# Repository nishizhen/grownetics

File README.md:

# Grownetics

Welcome to Grownetics Open Source repository.

Grownetics is a platform to help the world learn how to grow every plant better.

This repository will contain as much as we can possibly open source.

## Repository Status

Until recently all of our source was closed. We are moving to open as much of it as we can. As we do that, there will be problems, bugs, etc. This repository can be considered unstable.

# Handbook

[Grownetics Company Handbook](http://docs.grownetics.co/)

[Using our Documentation](http://docs.grownetics.co/documentation/)

# Technical Documentation

* [GrowServer](http://docs.grownetics.co/Development/growserver/)
* [Firmware](http://docs.grownetics.co/Development/firmware/)
* [GrowCtl](http://docs.grownetics.co/Development/growctl/)

# Reporting bugs

If you find a bug with the documentation, or something that could be improved, please open an [issue](https://code.cropcircle.io/Grownetics/Grownetics/issues).

# Community

Please join us and let us know what you think!

## [Chat](https://grownetics.zulipchat.com/)
## [Reddit](https://reddit.com/r/Grownetics/)
## [Twitch](https://www.twitch.tv/nickbusey/)

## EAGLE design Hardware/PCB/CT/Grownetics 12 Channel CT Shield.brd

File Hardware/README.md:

[< Documentation](../README.md)
# Hardware
### [Production](hardware-production.md)

### Arduino Software Setup
1. Download [VSCode](https://code.visualstudio.com/Download)  
2. Open the Extensions menu and install PlatformIO IDE (http://docs.platformio.org/en/latest/ide/vscode.html#installation)  
3. After platform.io is downloaded in vscode restart vscode, it will initiate the install, upon completion a bar comes on up top to restart vscode. You're in!  

### Git the Grownetics Repo   
1. Download and Install [git](http://git-scm.com/download/mac) (already installed on linux)  
2. 'cd' to the folder you want the Grownetics Repo to be in  
3. Check out the code (open Terminal and copy-paste)
`git clone git@code.cropcircle.io:Grownetics/Grownetics.git`
if you are unable to authenticate login to gitlab via code.cropcircle.io and add your .ssh public key to your profile settings. Then try again.  
4. Back in platform.io open the firmware folder you want to work with.  (i.e. the Middleware folder)
5. Navigate to the src folder once the project folder is open, click the Middleware.ino file
6. Build the file by clicking the tiny check mark at the bottom of the vscode window. 
7. You may have a missing library, this is where platform.io is awesome! Click the PIO Home tab
8. Click Libraries in the PIO left menu, search for the missing library (case and spaces matter!)
9. Click install, and try your build again, should be gtg!
5. Click the little right hand arrow at bottom of vscode to Upload it to the board.

### Arduino/Wifi-Reset Software Testing
1. Make sure you have the latest code by running `git pull` within the project folder.
2. Turn on Server/Pepwave, make sure TP-Links are synced, and make sure the Arduino Ethernet Shield has an ethernet cord out to the POE device connected to one of the TP-Links.
3. Verify/Upload the 'Middleware.x.x.x.ino' code to the Arduino.
4. Open the serial monitor (Cmd/Ctrl+Shift+M) and make sure data is accurately coming out AND that the server is sending a response back to the Arduino. 
  * ***Uploading code to the Arduino while the WiFi-Reset is ON can sometimes cause problems. Try uploading with the WiFi-Reset OFF.***  
  * ***The serial monitor has specific baud (data rate in bits per second) values that it receives output from. Make sure your serial monitor is set to the same baud value as in the code to see the correct output.***  

5. Verify/Upload the 'ESP8266_WiFi_Reset.x.x.x.ino' code directly to the WiFi-Reset module. 
6. Open the serial monitor and make sure it's getting a status code of 200 from the Server. If not, make sure the Access Point (Pepwave) login credentials match with the credentials in the wifi reset code.

7. The Arduino and WiFi Reset devices have been successfully tested, to be ready for production: Set debug = false, and assign an ID to the device (starting at 1).

## 3D Crop Sensor

3D Crop Device: onsite.grownetics.co port 81
Reset Device: onsite.grownetics.co port 82

Assembly: Devices should have already passed their individual QC test

Components required (Multiplexer shield, Ethernet shield, Arduino Mega)

*  Before assembly check that all pins are straight and undamaged
*  Match Pins on Arduino Mega with pins on Ethernet shield and connect devices
*  Attach multiplexer shield to the Ethernet shield 

QC Assesment (Device in NEMA box)

*  Make sure device has rubber studs or Velcro to secure it to the base of the NEMA box
*  Insert POE power cable into Arduino mega 
*  Insert other POE cable into Ethernet shield

## Suppliers

### Rapid PCB Suppliers
1. http://www.pcbway.com/f
2. http://www.pentalogix.com/pcb-manufacturing.php?gclid=CLmT5YOP_csCFQmSaQodgkoIUw
3. https://www.itead.cc/
4. http://www.customcircuitboards.com/
5. http://www.pcb-solutions.com/
6. http://www.pcbunlimited.com/
7. http://www.4pcb.com/
8. http://www.goldphoenixpcb.com/
9. http://www.seeedstudio.com/service/index.php?r=pcb

#### Pepwave Max BR-1
 * Support Contact:  taylor@frontierus.com, jgrote@frontierus.com, tel:866-226-6344
 * Default Wifi Password: Last 8 digits of LAN MAC.
 * Default admin login: admin/admin

* SIM Cards
 * Verizon Business Support:

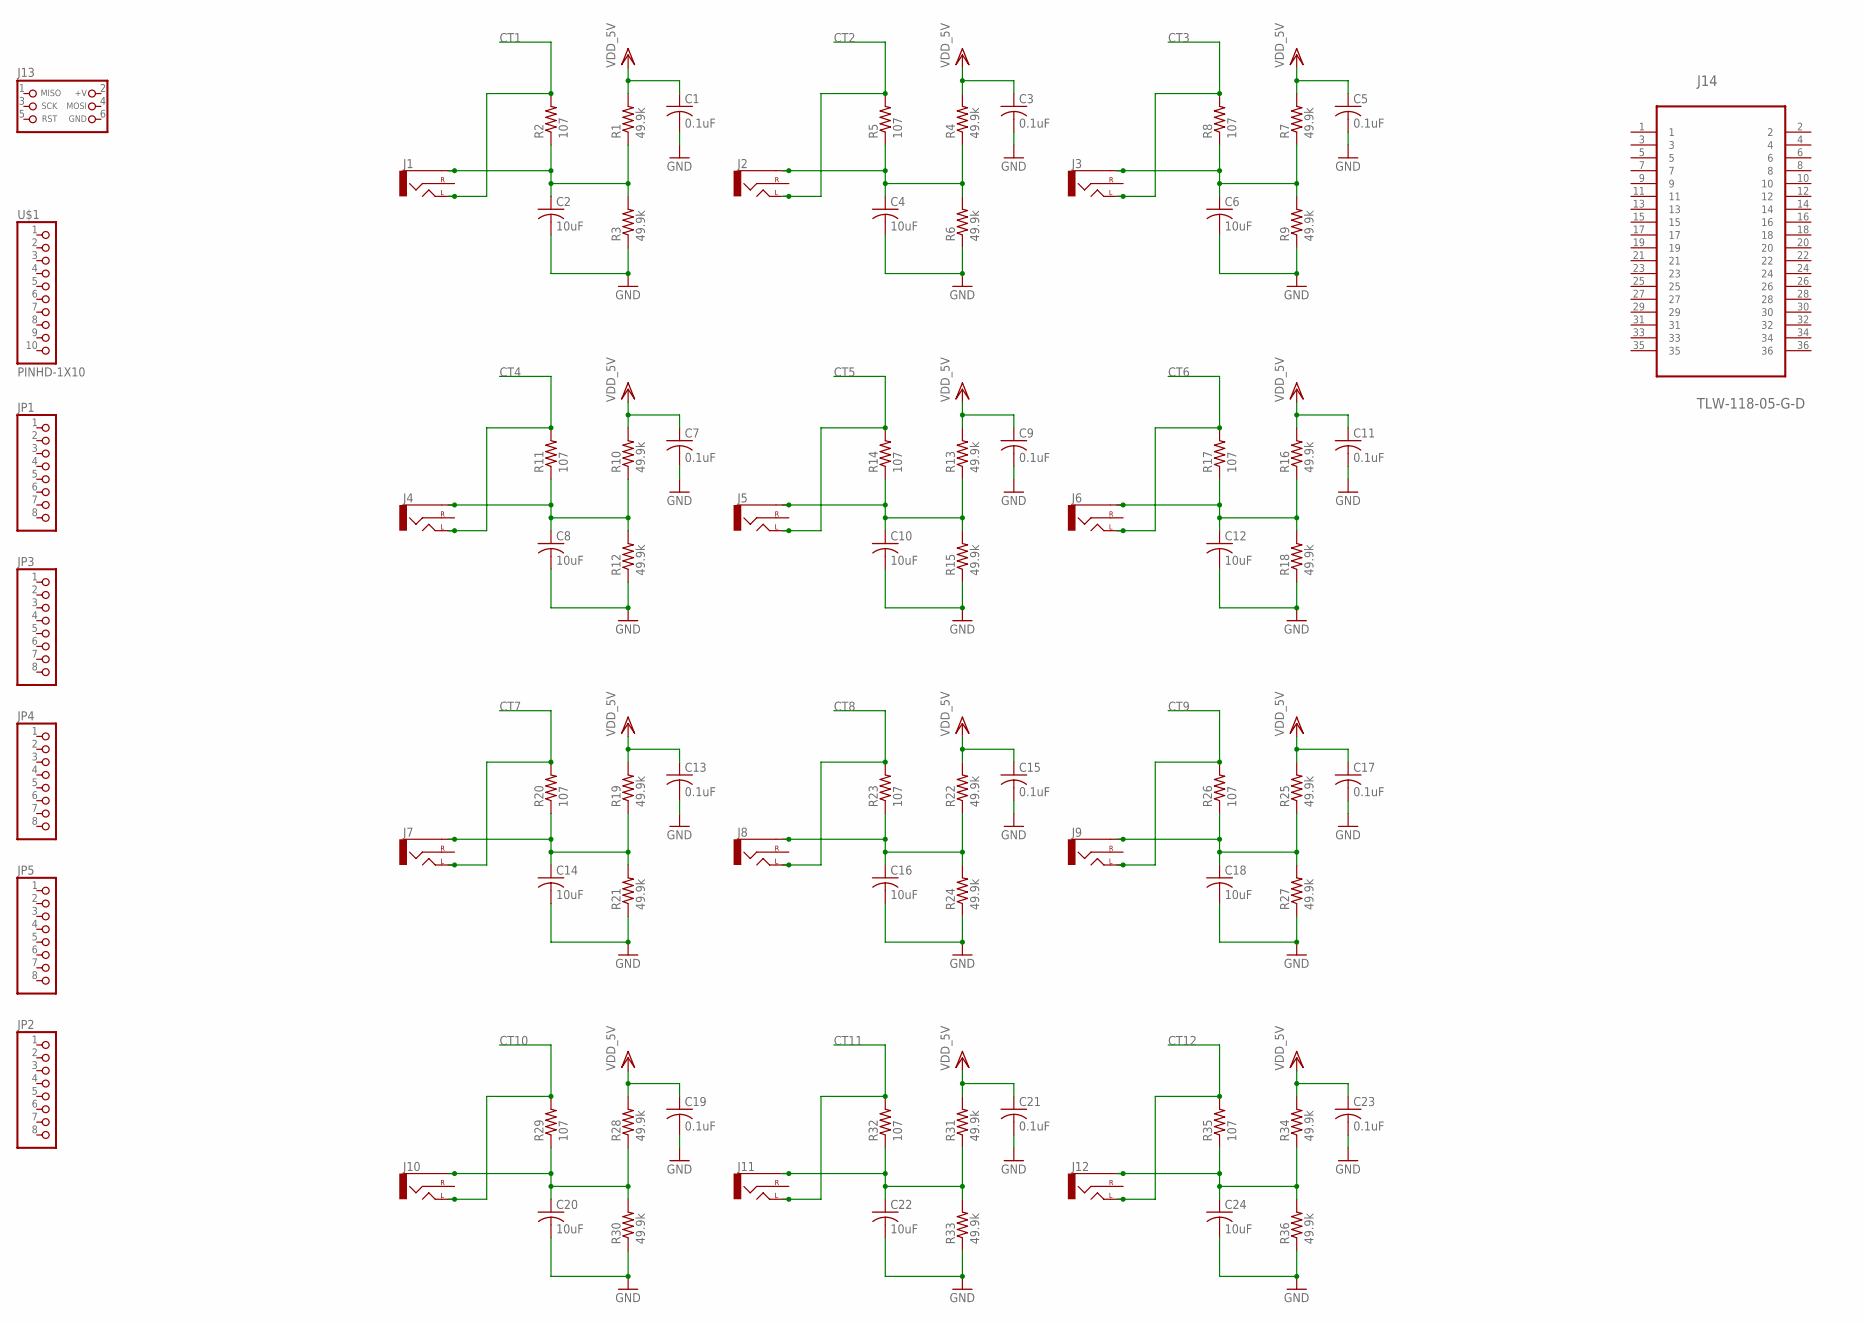
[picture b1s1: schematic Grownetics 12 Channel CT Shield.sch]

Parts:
C1, C3, C5, C7, C9, C11, C13, C15, C17, C19, C21, C23: 0.1uF; C0805
C2, C4, C6, C8, C10, C12, C14, C16, C18, C20, C22, C24: 10uF; C0805
J1, J2, J3, J4, J5, J6, J7, J8, J9, J10, J11, J12: AUDIO-JACKSMD2; AUDIO-JACK-3.5MM-SMD
J13: CON_HEADER_PRG_AVR_ICSP-PTH; HEADER_PRG_2X03
J14: TLW-118-05-G-D; SAMTEC_TLW-118-05-G-D
JP1, JP2, JP3, JP4, JP5: PINHD-1X8-3.5MM; 1X08-3.5MM
R1, R3, R4, R6, R7, R9, R10, R12, R13, R15, R16, R18, R19, R21, R22, R24, R25, R27, R28, R30, R31, R33, R34, R36: 49.9k; M0805
R2, R5, R8, R11, R14, R17, R20, R23, R26, R29, R32, R35: 107; M0805
U$1: PINHD-1X10; 1X10-BIG

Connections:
CT1: J1.TIP (LEFT), R2.2
CT2: J2.TIP (LEFT), R5.2
CT3: J3.TIP (LEFT), R8.2
CT4: J4.TIP (LEFT), R11.2
CT5: J5.TIP (LEFT), R14.2
CT6: J6.TIP (LEFT), R17.2
CT7: J7.TIP (LEFT), R20.2
CT8: J8.TIP (LEFT), R23.2
CT9: J9.TIP (LEFT), R26.2
CT10: J10.TIP (LEFT), R29.2
CT11: J11.TIP (LEFT), R32.2
CT12: J12.TIP (LEFT), R35.2
GND: C1.2, C2.2, C3.2, C4.2, C5.2, C6.2, C7.2, C8.2, C9.2, C10.2, C11.2, C12.2, C13.2, C14.2, C15.2, C16.2, C17.2, C18.2, C19.2, C20.2, C21.2, C22.2, C23.2, C24.2, R3.1, R6.1, R9.1, R12.1, R15.1, R18.1, R21.1, R24.1, R27.1, R30.1, R33.1, R36.1
unnamed: C4.1, J2.SLEEVE, R4.1, R5.1, R6.2
unnamed: C2.1, J1.SLEEVE, R1.1, R2.1, R3.2
unnamed: C6.1, J3.SLEEVE, R7.1, R8.1, R9.2
unnamed: C8.1, J4.SLEEVE, R10.1, R11.1, R12.2
unnamed: C10.1, J5.SLEEVE, R13.1, R14.1, R15.2
unnamed: C12.1, J6.SLEEVE, R16.1, R17.1, R18.2
unnamed: C14.1, J7.SLEEVE, R19.1, R20.1, R21.2
unnamed: C16.1, J8.SLEEVE, R22.1, R23.1, R24.2
unnamed: C18.1, J9.SLEEVE, R25.1, R26.1, R27.2
unnamed: C20.1, J10.SLEEVE, R28.1, R29.1, R30.2
unnamed: C22.1, J11.SLEEVE, R31.1, R32.1, R33.2
unnamed: C24.1, J12.SLEEVE, R34.1, R35.1, R36.2
VDD: C1.1, C3.1, C5.1, C7.1, C9.1, C11.1, C13.1, C15.1, C17.1, C19.1, C21.1, C23.1, R1.2, R4.2, R7.2, R10.2, R13.2, R16.2, R19.2, R22.2, R25.2, R28.2, R31.2, R34.2

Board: 2 copper layers, 80 parts (0 on the bottom side), 26 nets, no tracks yet.

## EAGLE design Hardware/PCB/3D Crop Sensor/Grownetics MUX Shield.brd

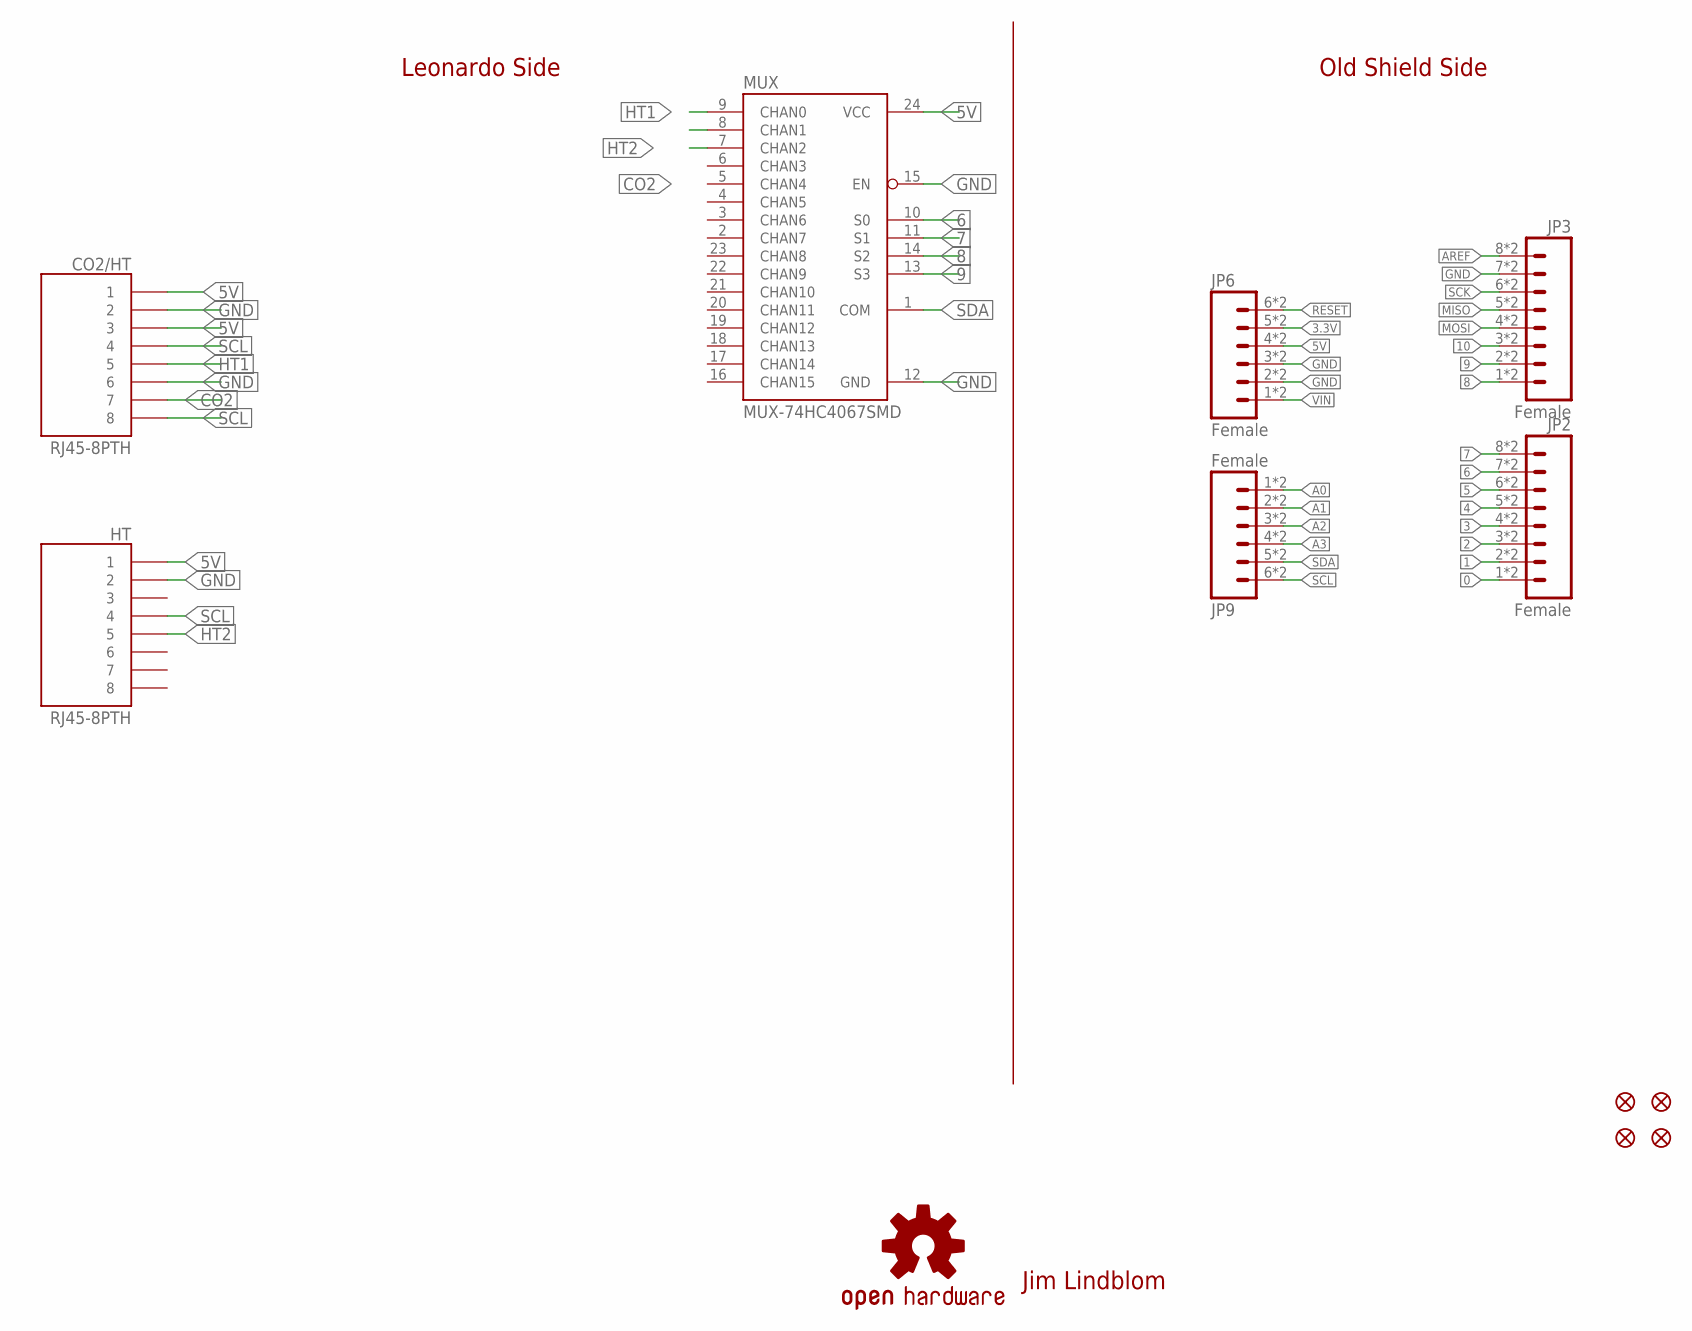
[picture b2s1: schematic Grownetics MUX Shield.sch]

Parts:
CO2/HT: RJ45-8PTH; RJ45-8
HT: RJ45-8PTH; RJ45-8
JP2, JP3: Female; 1X08_SMD_COMBINED
JP6, JP9: Female; 1X06_SMD_STRAIGHT_COMBO
JP11, JP12, JP13, JP14: FIDUCIALUFIDUCIAL; MICRO-FIDUCIAL
MUX: MUX-74HC4067SMD; SSOP24
U$1: OSHW-LOGOS; OSHW-LOGO-S

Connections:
0: JP2.1, JP2.1@2 (1)
1: JP2.2, JP2.2@2 (2)
2: JP2.3, JP2.3@2 (3)
3: JP2.4, JP2.4@2 (4)
3.3V: JP6.5, JP6.5-2 (5)
4: JP2.5, JP2.5@2 (5)
5: JP2.6, JP2.6@2 (6)
5V: CO2/HT.1, CO2/HT.3, HT.1, JP6.4, JP6.4-2 (4), MUX.24 (VCC)
6: JP2.7, JP2.7@2 (7), MUX.10 (S0)
7: JP2.8, JP2.8@2 (8), MUX.11 (S1)
8: JP3.1, JP3.1@2 (1), MUX.14 (S2)
9: JP3.2, JP3.2@2 (2), MUX.13 (S3)
10: JP3.3, JP3.3@2 (3)
A0: JP9.1, JP9.1-2 (1)
A1: JP9.2, JP9.2-2 (2)
A2: JP9.3, JP9.3-2 (3)
A3: JP9.4, JP9.4-2 (4)
AREF: JP3.8, JP3.8@2 (8)
CO2: CO2/HT.7, MUX.7 (CHAN2)
GND: CO2/HT.2, CO2/HT.6, HT.2, JP3.7, JP3.7@2 (7), JP6.2, JP6.2-2 (2), JP6.3, JP6.3-2 (3), MUX.12 (GND), MUX.15 (EN)
HT1: CO2/HT.5, MUX.9 (CHAN0)
HT2: HT.5, MUX.8 (CHAN1)
MISO: JP3.5, JP3.5@2 (5)
MOSI: JP3.4, JP3.4@2 (4)
RESET: JP6.6, JP6.6-2 (6)
SCK: JP3.6, JP3.6@2 (6)
SCL: CO2/HT.4, CO2/HT.8, HT.4, JP9.6, JP9.6-2 (6)
SDA: JP9.5, JP9.5-2 (5), MUX.1 (COM)
VIN: JP6.1, JP6.1-2 (1)

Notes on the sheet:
Jim Lindblom
Leonardo Side
Old Shield Side

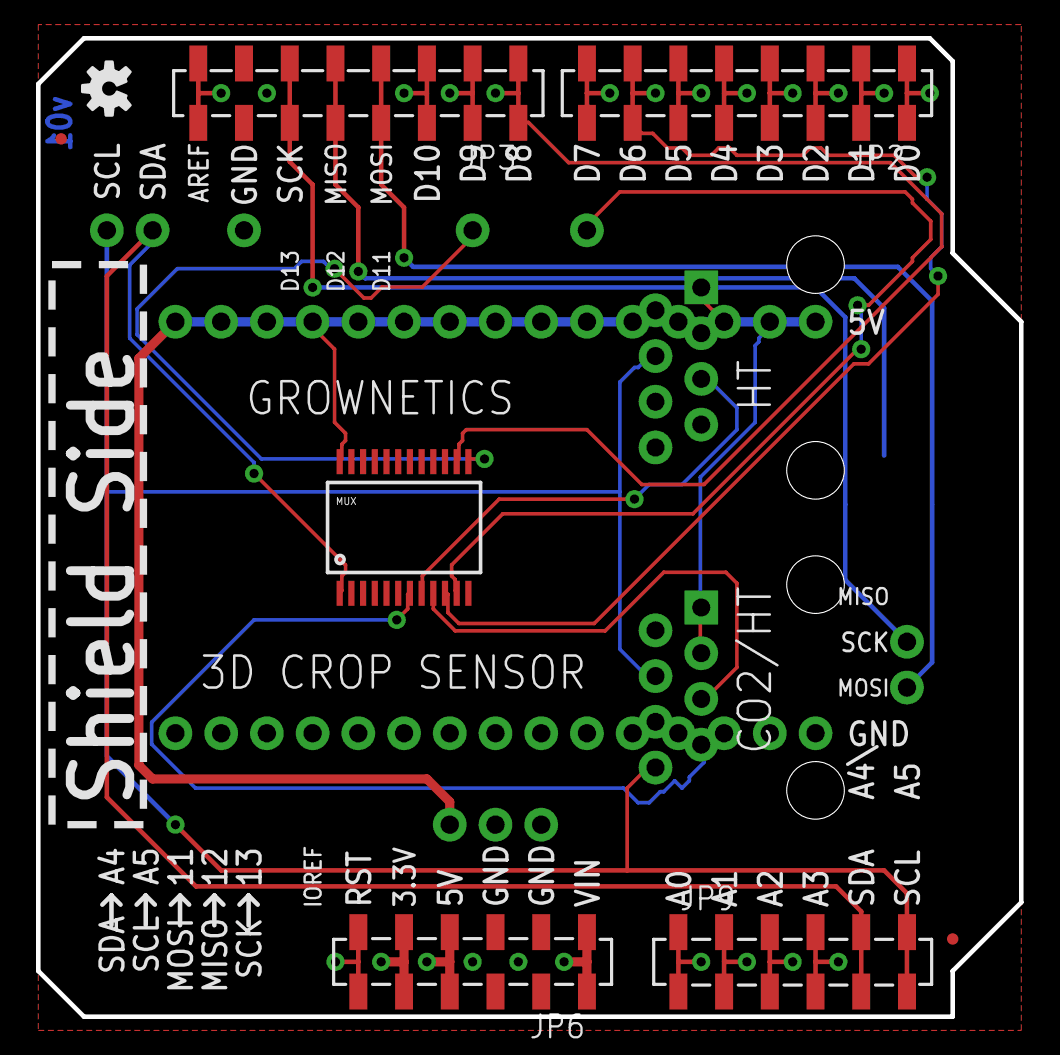
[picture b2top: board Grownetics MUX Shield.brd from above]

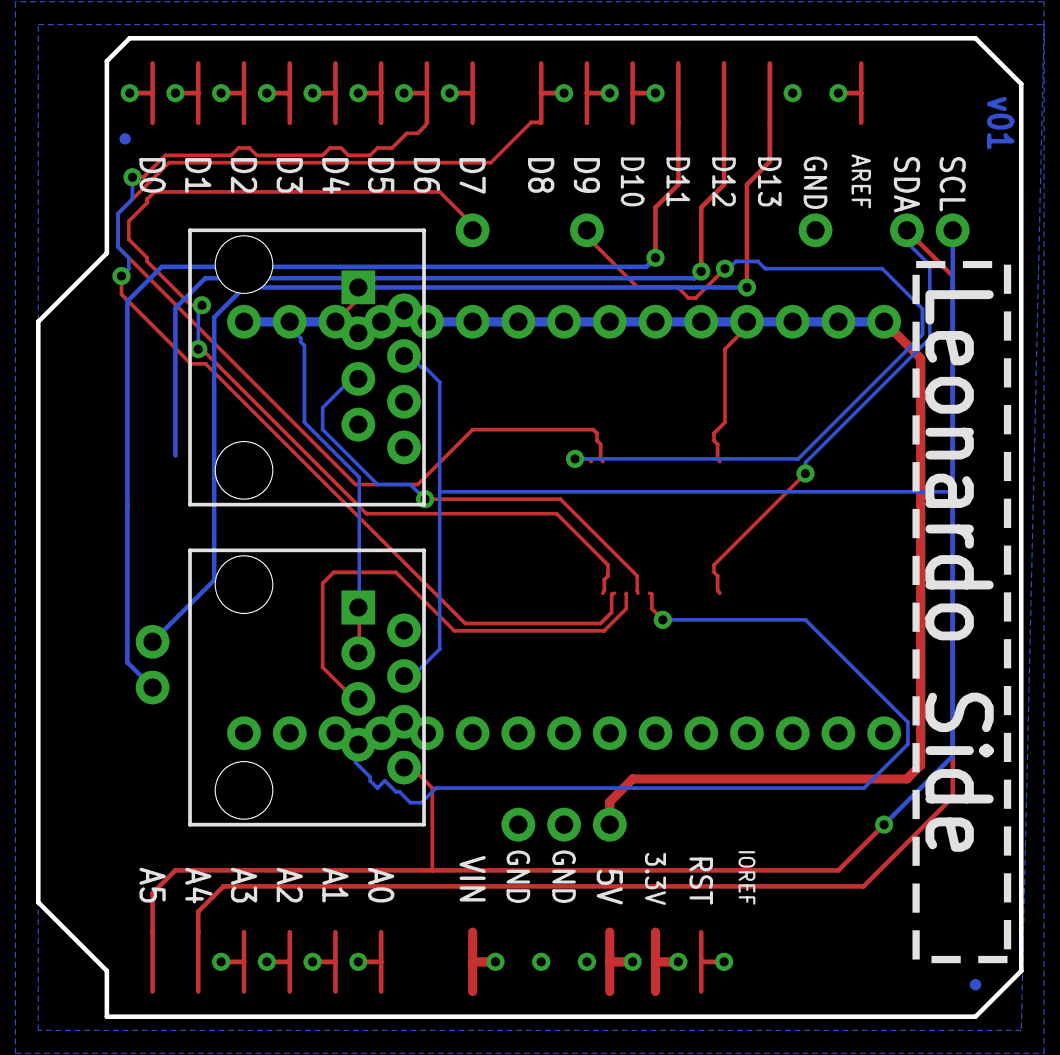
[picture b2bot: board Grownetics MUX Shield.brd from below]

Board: 2 copper layers, 54.6 x 54.4 mm, 12 parts (4 on the bottom side), 29 nets.

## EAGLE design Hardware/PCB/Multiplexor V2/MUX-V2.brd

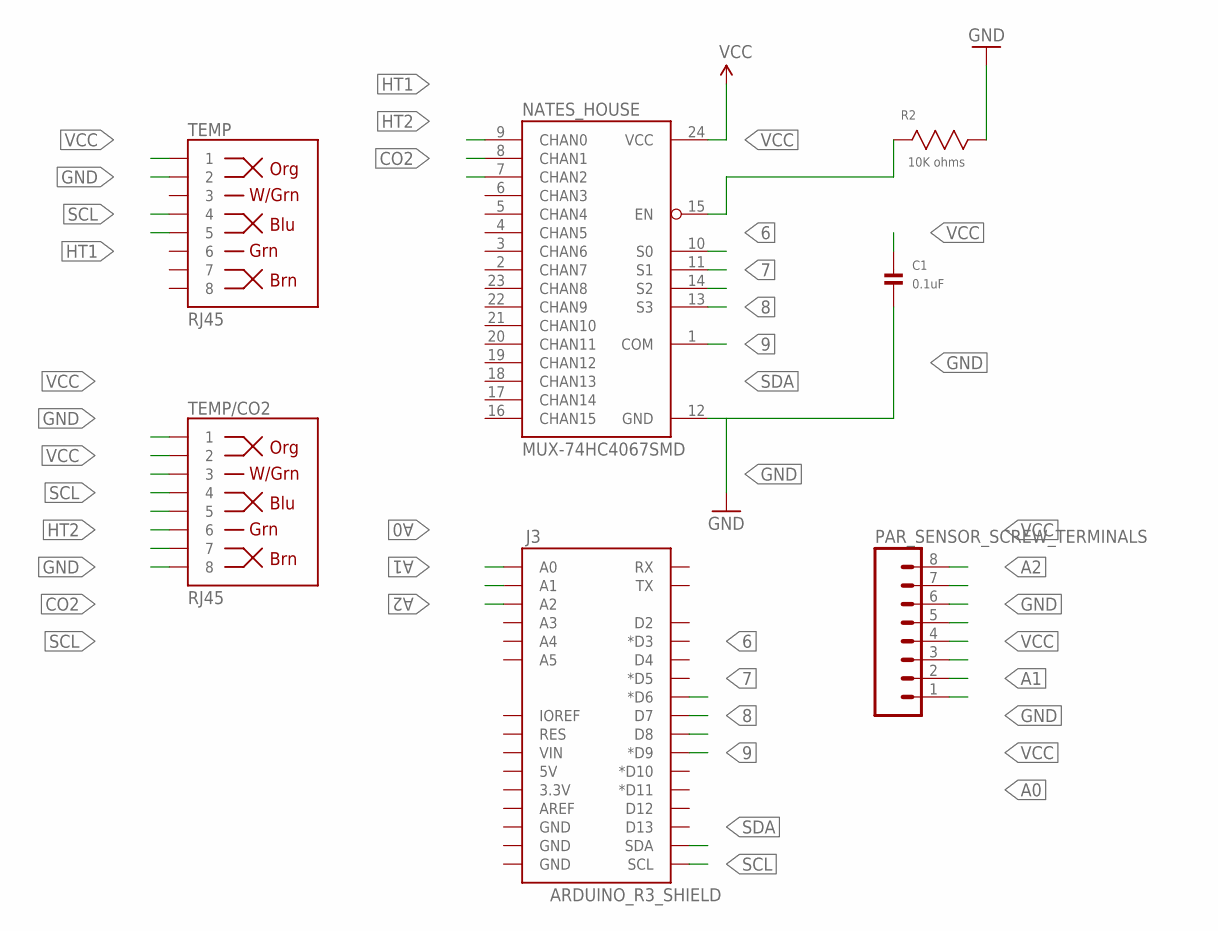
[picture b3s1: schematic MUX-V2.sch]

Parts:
C1: 0.1uF; _0805
J3: ARDUINO_R3_SHIELD; UNO_R3_SHIELD
NATES_HOUSE: MUX-74HC4067SMD; SSOP24
PAR_SENSOR_SCREW_TERMINALS: M083.5MM-8; SCREWTERMINAL-3.5MM-8
R2: 10K ohms; RESC2013X65N
TEMP: RJ45; RJ45-8
TEMP/CO2: RJ45; RJ45-8

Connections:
6: J3.D6 (*D6), NATES_HOUSE.10 (S0)
7: J3.D7, NATES_HOUSE.11 (S1)
8: J3.D8, NATES_HOUSE.14 (S2)
9: J3.D9 (*D9), NATES_HOUSE.13 (S3)
12: R2.1 (R1)
A0: J3.A0, PAR_SENSOR_SCREW_TERMINALS.1
A1: J3.A1, PAR_SENSOR_SCREW_TERMINALS.4
A2: J3.A2, PAR_SENSOR_SCREW_TERMINALS.7
CO2: NATES_HOUSE.7 (CHAN2), TEMP/CO2.7
GND: C1.2, NATES_HOUSE.12 (GND), PAR_SENSOR_SCREW_TERMINALS.3, PAR_SENSOR_SCREW_TERMINALS.6, TEMP.2, TEMP/CO2.2, TEMP/CO2.6
HT1: NATES_HOUSE.9 (CHAN0), TEMP.5
HT2: NATES_HOUSE.8 (CHAN1), TEMP/CO2.5
unnamed: NATES_HOUSE.15 (EN), R2.2 (R2)
SCL: J3.SCL, TEMP.4, TEMP/CO2.4, TEMP/CO2.8
SDA: J3.SDA, NATES_HOUSE.1 (COM)
VCC: C1.1, NATES_HOUSE.24 (VCC), PAR_SENSOR_SCREW_TERMINALS.2, PAR_SENSOR_SCREW_TERMINALS.5, PAR_SENSOR_SCREW_TERMINALS.8, TEMP.1, TEMP/CO2.1, TEMP/CO2.3

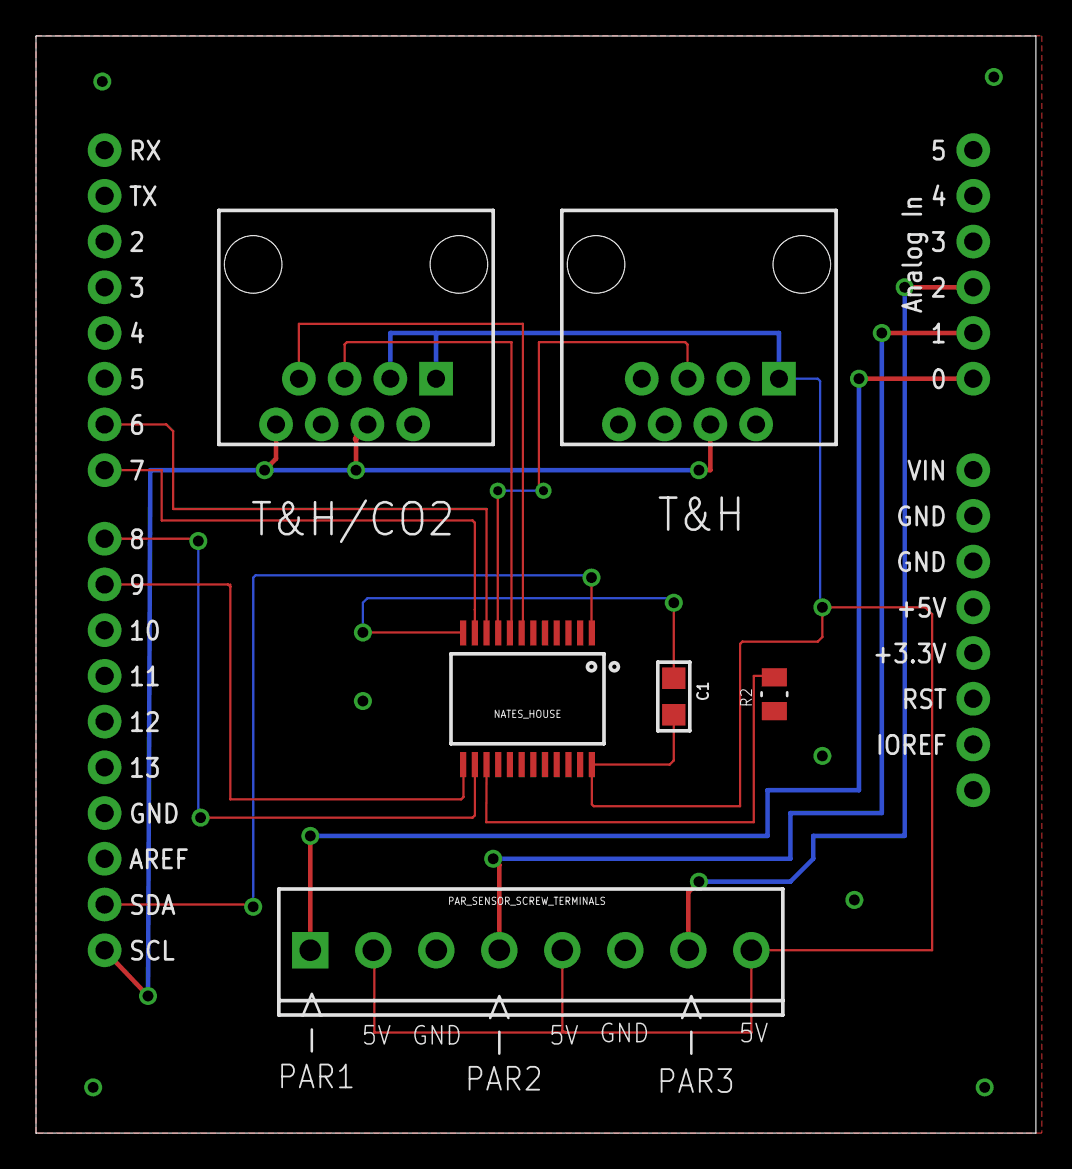
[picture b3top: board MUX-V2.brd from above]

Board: 2 copper layers, 55.6 x 61.0 mm, 7 parts (0 on the bottom side), 15 nets.

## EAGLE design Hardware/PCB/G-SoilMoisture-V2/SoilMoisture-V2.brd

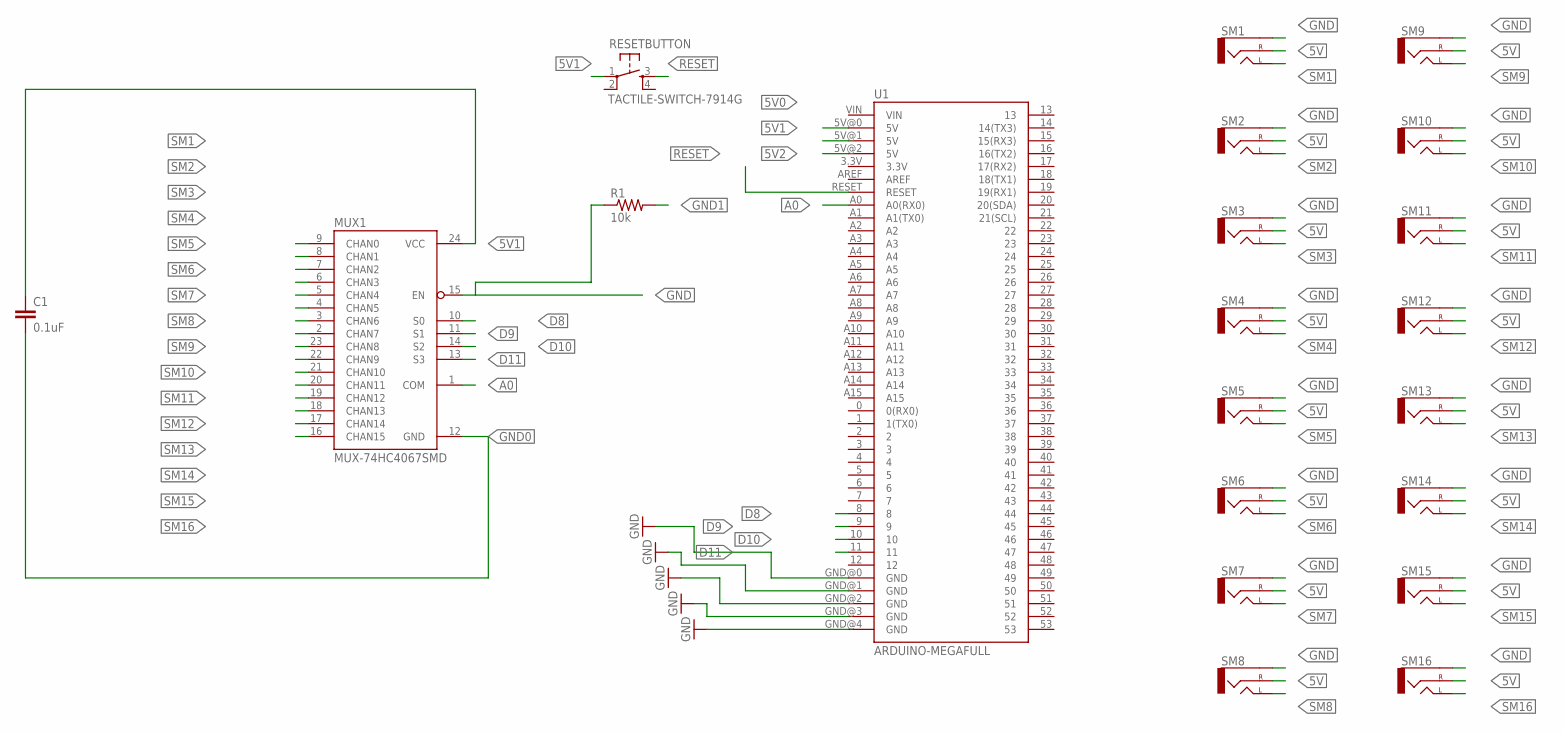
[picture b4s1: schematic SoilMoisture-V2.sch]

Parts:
C1: 0.1uF; 0603-CAP
MUX1: MUX-74HC4067SMD; SSOP24
R1: 10k; 0402-RES
RESETBUTTON: TACTILE-SWITCH-7914G; 7914G
SM1, SM2, SM3, SM4, SM5, SM6, SM7, SM8, SM9, SM10, SM11, SM12, SM13, SM14, SM15, SM16: AUDIO-JACKPTH; AUDIO-JACK
U1: ARDUINO-MEGAFULL; ARDUINO_MEGA

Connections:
5V: SM1.RING (RIGHT), SM2.RING (RIGHT), SM3.RING (RIGHT), SM4.RING (RIGHT), SM5.RING (RIGHT), SM6.RING (RIGHT), SM7.RING (RIGHT), SM8.RING (RIGHT), SM9.RING (RIGHT), SM10.RING (RIGHT), SM11.RING (RIGHT), SM12.RING (RIGHT), SM13.RING (RIGHT), SM14.RING (RIGHT), SM15.RING (RIGHT), SM16.RING (RIGHT)
5V0: U1.5V@0 (5V)
5V1: C1.1, MUX1.24 (VCC), RESETBUTTON.1, U1.5V@1 (5V)
5V2: U1.5V@2 (5V)
A0: MUX1.1 (COM), U1.A0 (A0(RX0))
D8: MUX1.10 (S0), U1.8
D9: MUX1.11 (S1), U1.9
D10: MUX1.14 (S2), U1.10
D11: MUX1.13 (S3), U1.11, U1.GND@2 (GND)
GND: MUX1.15 (EN), R1.1, SM1.SLEEVE, SM2.SLEEVE, SM3.SLEEVE, SM4.SLEEVE, SM5.SLEEVE, SM6.SLEEVE, SM7.SLEEVE, SM8.SLEEVE, SM9.SLEEVE, SM10.SLEEVE, SM11.SLEEVE, SM12.SLEEVE, SM13.SLEEVE, SM14.SLEEVE, SM15.SLEEVE, SM16.SLEEVE, U1.GND@0 (GND), U1.GND@1 (GND), U1.GND@3 (GND), U1.GND@4 (GND)
GND0: C1.2, MUX1.12 (GND)
GND1: R1.2
RESET: RESETBUTTON.3, U1.RESET
SM1: MUX1.9 (CHAN0), SM1.TIP (LEFT)
SM2: MUX1.8 (CHAN1), SM2.TIP (LEFT)
SM3: MUX1.7 (CHAN2), SM3.TIP (LEFT)
SM4: MUX1.6 (CHAN3), SM4.TIP (LEFT)
SM5: MUX1.5 (CHAN4), SM5.TIP (LEFT)
SM6: MUX1.4 (CHAN5), SM6.TIP (LEFT)
SM7: MUX1.3 (CHAN6), SM7.TIP (LEFT)
SM8: MUX1.2 (CHAN7), SM8.TIP (LEFT)
SM9: MUX1.23 (CHAN8), SM9.TIP (LEFT)
SM10: MUX1.22 (CHAN9), SM10.TIP (LEFT)
SM11: MUX1.21 (CHAN10), SM11.TIP (LEFT)
SM12: MUX1.20 (CHAN11), SM12.TIP (LEFT)
SM13: MUX1.19 (CHAN12), SM13.TIP (LEFT)
SM14: MUX1.18 (CHAN13), SM14.TIP (LEFT)
SM15: MUX1.17 (CHAN14), SM15.TIP (LEFT)
SM16: MUX1.16 (CHAN15), SM16.TIP (LEFT)

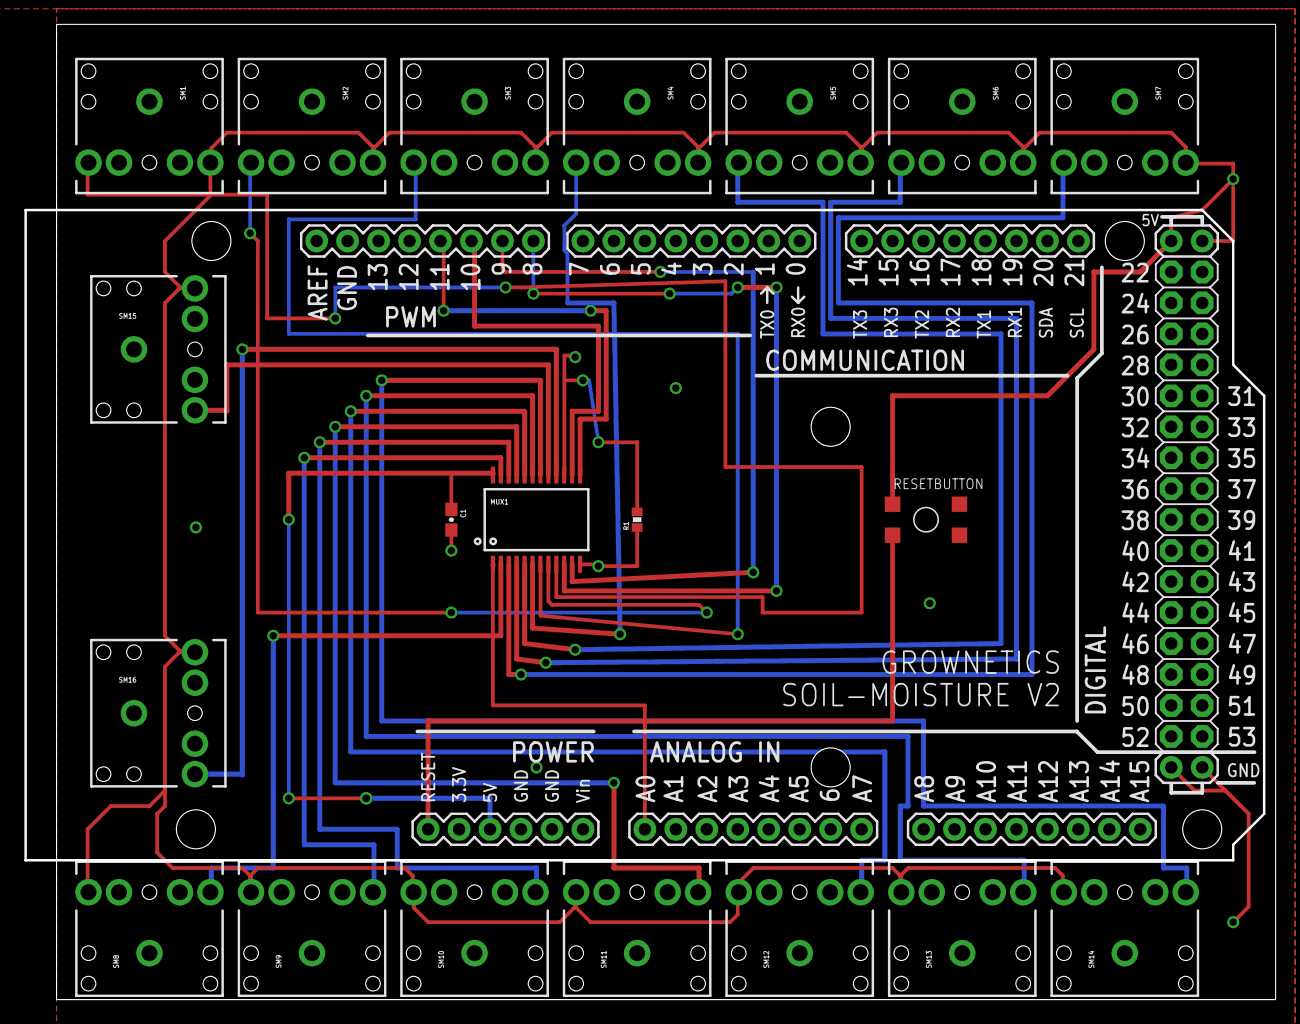
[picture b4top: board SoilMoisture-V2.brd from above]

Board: 2 copper layers, 102.4 x 79.8 mm, 21 parts (0 on the bottom side), 26 nets.

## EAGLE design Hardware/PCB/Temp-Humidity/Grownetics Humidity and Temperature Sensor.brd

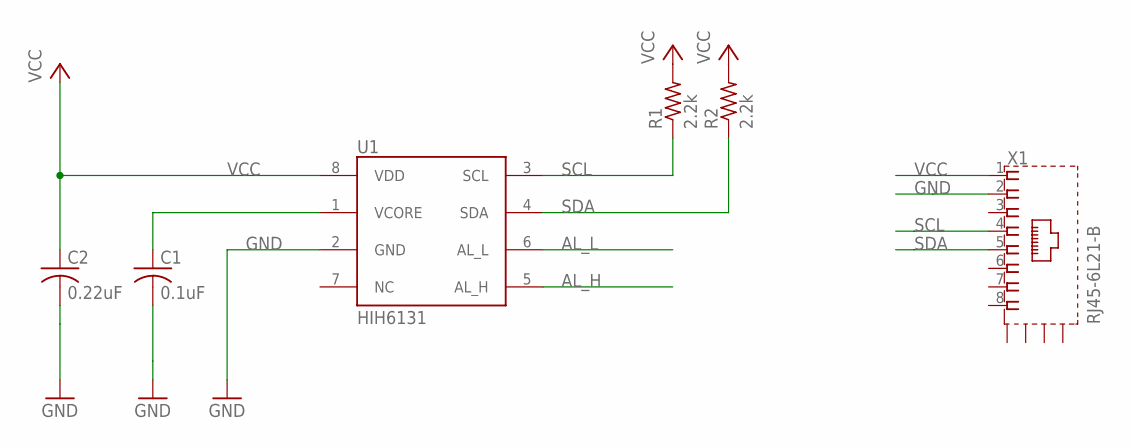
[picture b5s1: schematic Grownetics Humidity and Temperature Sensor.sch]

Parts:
C1: 0.1uF; C0805; MPN C0805S104K5RACAUTO
C2: 0.22uF; C0805; MPN C0805X224K5RACTU
R1, R2: 2.2k; R0805; MPN SR1-0805-222
U1: HIH6131; SOIC8; MPN HIH6131-021-001
X1: RJ45-6L21-B; RJ45-SHIELD1; MPN RJE71-188-1401

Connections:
AL_H: U1.5 (AL_H)
AL_L: U1.6 (AL_L)
GND: C1.2, C2.2, U1.2 (GND), X1.2
SCL: R1.1, U1.3 (SCL), X1.4
SDA: R2.1, U1.4 (SDA), X1.5
VCC: C2.1, R1.2, R2.2, U1.8 (VDD), X1.1
VCORE: C1.1, U1.1 (VCORE)

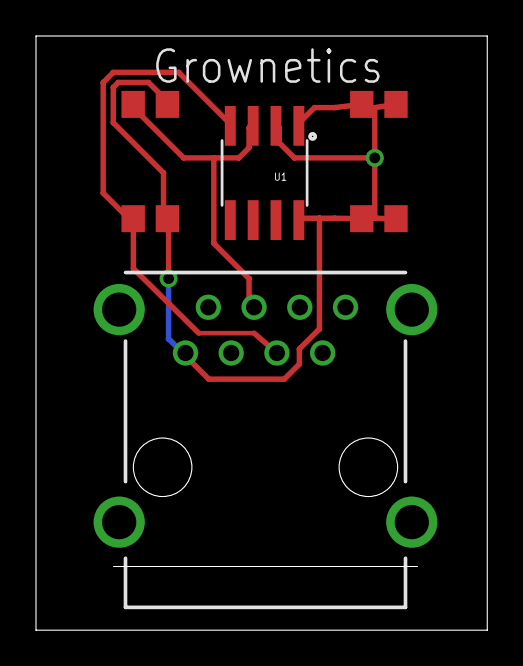
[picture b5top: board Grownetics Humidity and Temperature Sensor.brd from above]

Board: 2 copper layers, 25.1 x 33.0 mm, 6 parts (0 on the bottom side), 5 nets.

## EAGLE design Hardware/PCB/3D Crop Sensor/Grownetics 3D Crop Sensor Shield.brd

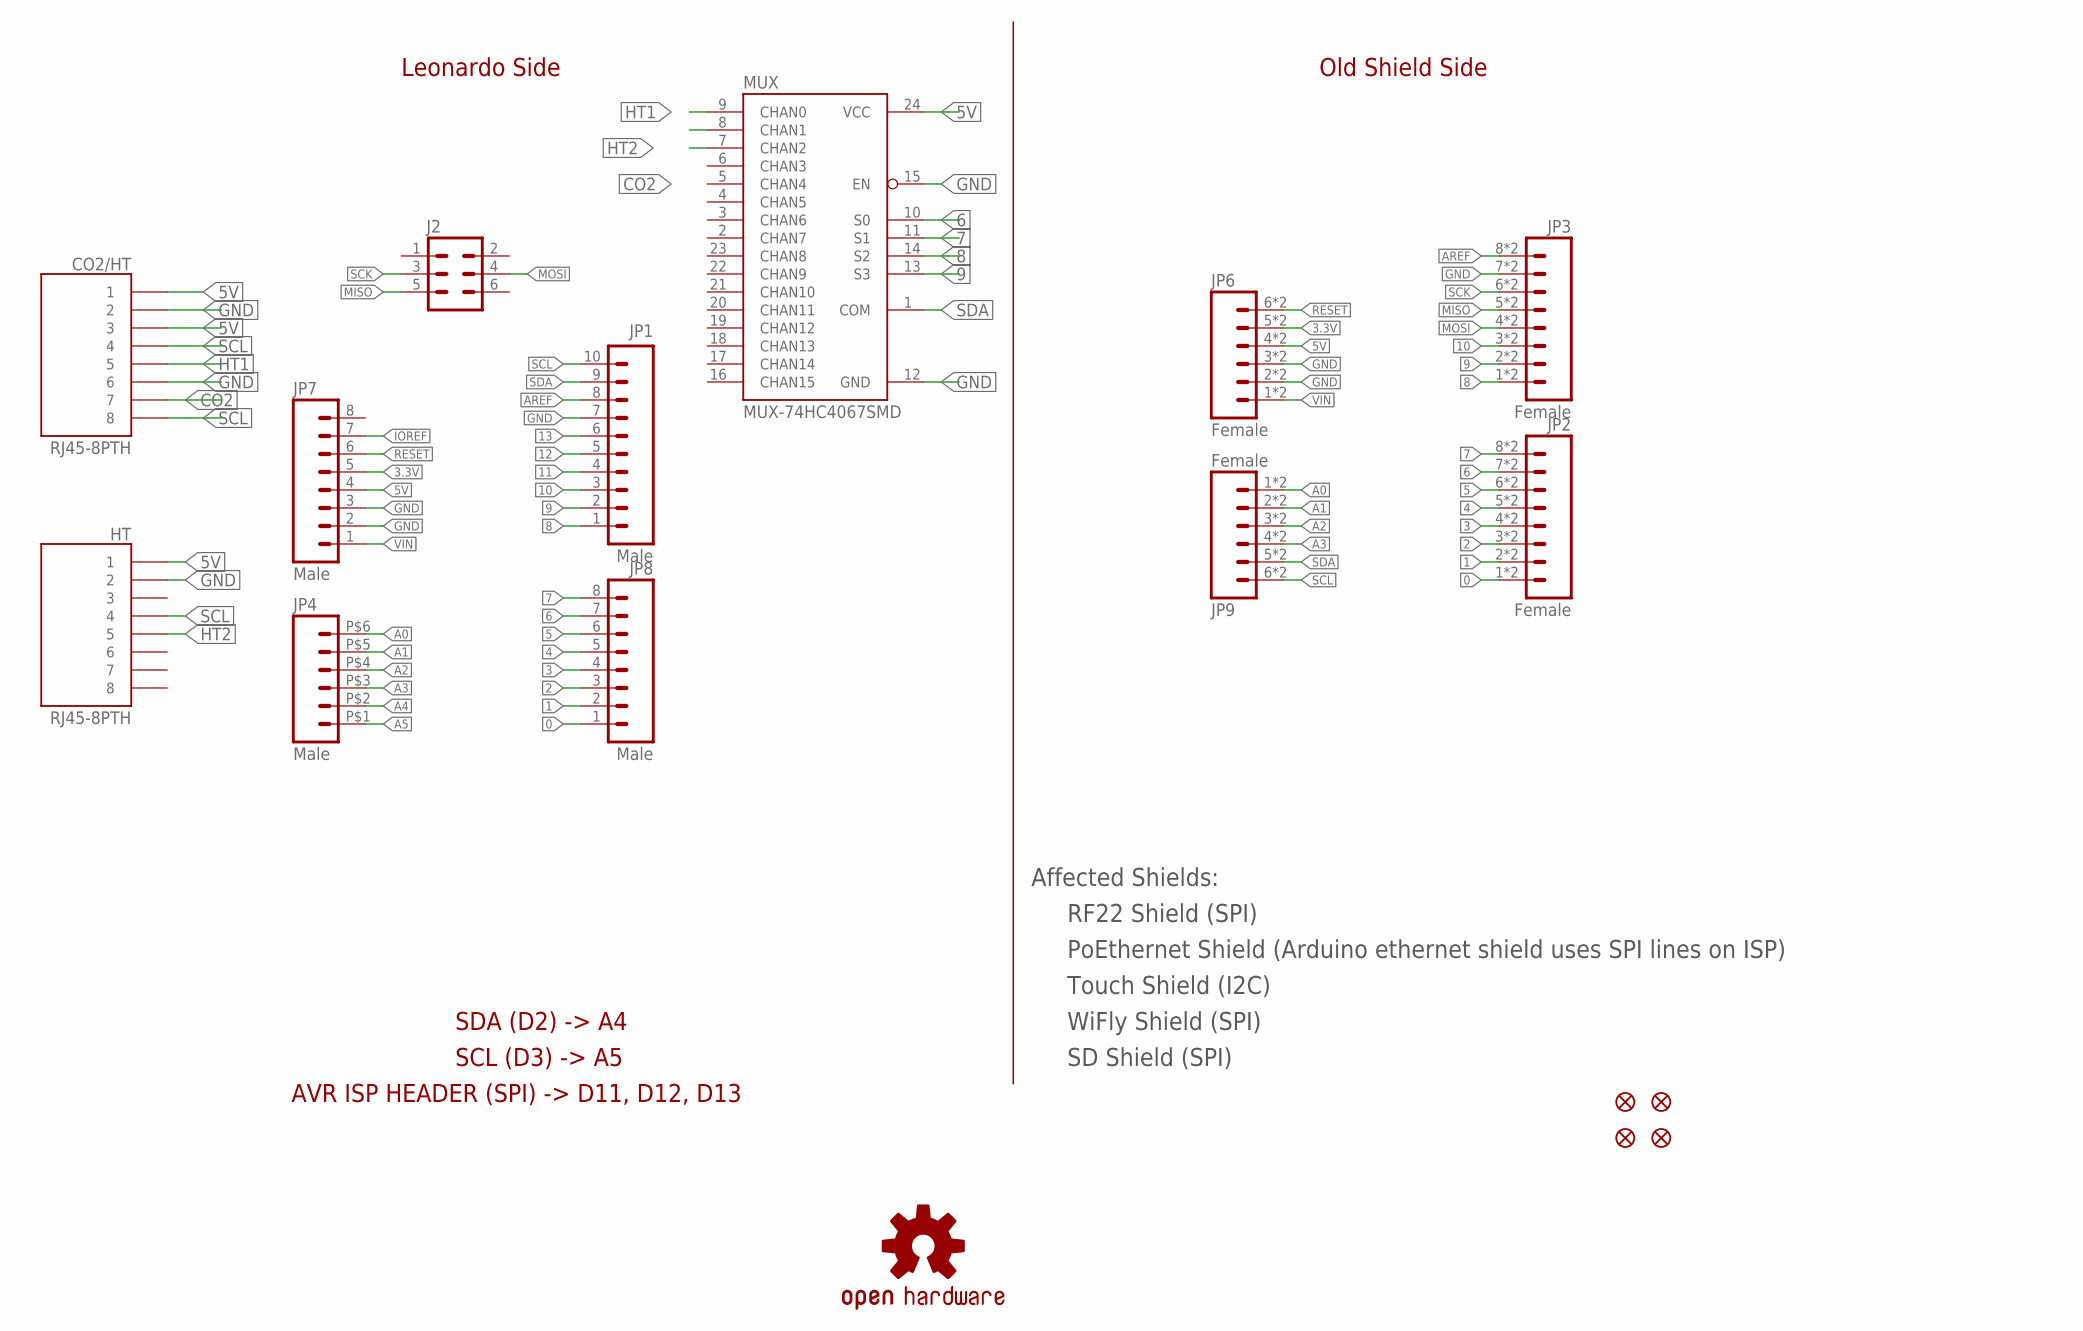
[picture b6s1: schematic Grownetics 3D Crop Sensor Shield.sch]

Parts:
CO2/HT: RJ45-8PTH; RJ45-8
HT: RJ45-8PTH; RJ45-8
J2: Female; 2X3_SMD
JP1: Male; 1X10_SMD_MALE
JP2, JP3: Female; 1X08_SMD_COMBINED
JP4: Male; 1X06_SMD_MALE
JP6, JP9: Female; 1X06_SMD_STRAIGHT_COMBO
JP7, JP8: Male; 1X08_SMD_MALE
JP11, JP12, JP13, JP14: FIDUCIALUFIDUCIAL; MICRO-FIDUCIAL
MUX: MUX-74HC4067SMD; SSOP24
U$1: OSHW-LOGOS; OSHW-LOGO-S

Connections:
0: JP2.1, JP2.1@2 (1), JP8.1
1: JP2.2, JP2.2@2 (2), JP8.2
2: JP2.3, JP2.3@2 (3), JP8.3
3: JP2.4, JP2.4@2 (4), JP8.4
3.3V: JP6.5, JP6.5-2 (5), JP7.5
4: JP2.5, JP2.5@2 (5), JP8.5
5: JP2.6, JP2.6@2 (6), JP8.6
5V: CO2/HT.1, CO2/HT.3, HT.1, JP6.4, JP6.4-2 (4), JP7.4, MUX.24 (VCC)
6: JP2.7, JP2.7@2 (7), JP8.7, MUX.10 (S0)
7: JP2.8, JP2.8@2 (8), JP8.8, MUX.11 (S1)
8: JP1.1, JP3.1, JP3.1@2 (1), MUX.14 (S2)
9: JP1.2, JP3.2, JP3.2@2 (2), MUX.13 (S3)
10: JP1.3, JP3.3, JP3.3@2 (3)
11: JP1.4
12: JP1.5
13: JP1.6
A0: JP4.P$6 (6), JP9.1, JP9.1-2 (1)
A1: JP4.P$5 (5), JP9.2, JP9.2-2 (2)
A2: JP4.P$4 (4), JP9.3, JP9.3-2 (3)
A3: JP4.P$3 (3), JP9.4, JP9.4-2 (4)
A4: JP4.P$2 (2)
A5: JP4.P$1 (1)
AREF: JP1.8, JP3.8, JP3.8@2 (8)
CO2: CO2/HT.7, MUX.7 (CHAN2)
GND: CO2/HT.2, CO2/HT.6, HT.2, JP1.7, JP3.7, JP3.7@2 (7), JP6.2, JP6.2-2 (2), JP6.3, JP6.3-2 (3), JP7.2, JP7.3, MUX.12 (GND), MUX.15 (EN)
HT1: CO2/HT.5, MUX.9 (CHAN0)
HT2: HT.5, MUX.8 (CHAN1)
IOREF: JP7.7
MISO: J2.5, JP3.5, JP3.5@2 (5)
MOSI: J2.4, JP3.4, JP3.4@2 (4)
RESET: JP6.6, JP6.6-2 (6), JP7.6
SCK: J2.3, JP3.6, JP3.6@2 (6)
SCL: CO2/HT.4, CO2/HT.8, HT.4, JP1.10, JP9.6, JP9.6-2 (6)
SDA: JP1.9, JP9.5, JP9.5-2 (5), MUX.1 (COM)
VIN: JP6.1, JP6.1-2 (1), JP7.1

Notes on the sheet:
Affected Shields:
RF22 Shield (SPI)
PoEthernet Shield (Arduino ethernet shield uses SPI lines on ISP)
Touch Shield (I2C)
WiFly Shield (SPI)
SD Shield (SPI)
Leonardo Side
Old Shield Side
SDA (D2) -> A4
SCL (D3) -> A5
AVR ISP HEADER (SPI) -> D11, D12, D13

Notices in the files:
parts and their libraries:
SparkFun-Aesthetics: Licensing: CC v3.0 Share-Alike You are welcome to use this library for commercial purposes.
SparkFun-Aesthetics: Released under the Creative Commons
SparkFun-Aesthetics: http://creativecommons.org/licenses/by-sa/3.0
